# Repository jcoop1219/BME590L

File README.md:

# BME590L_Lightbulb - Design Skills Project (Variable Light Intensity)

See Final Working Video on [YouTube](https://youtu.be/NFrjT-VMIhY).

## Usage Guide
1. Turn on device using red I/O switch.
1. Push white button closest to I/O switch to cycle through light modes:
   + `Off`
   + `Brightest`
   + `Intermediate Brightness`
   + `Least Bright`
   + `Flashing @ 2 Hz`
1. Push and hold white button furthest from I/O switch to show the remaining voltage left in the battery on the adjacent LED:
   + `GREEN` = battery high (>8V)
   + `BLUE` = battery medium (7-8V)
   + `RED` = battery low (<7V)

## Battery Replacement
1. Spin flaps on bottom away from center of device.
1. Pull top of case off of bottom of case and disconnect toggle switch Molex connection from board.
1. Remove battery wire Molex connection from board.
1. Remove battery from battery slot.
1. Detach wired cap from battery.
1. Attach wired cap to new battery.
1. Add new battery to battery slot.
1. Re-attach battery wire Molex connection to board.
1. Reconnect toggle switch Molex connection to board.
1. Replace case top over case bottom (note: may need to use tweezers or small object to guide push buttons through case top).
1. Spin flaps on bottom towards center of device.

## Documentation
1. [Bill of Materials](https://github.com/jcoop1219/BME590L_Lightbulb/blob/master/Documentation/Bill%20of%20Materials.xlsx)
1. [Final Device Photos](https://github.com/jcoop1219/BME590L_Lightbulb/tree/master/Documentation/Final%20Device%20Photos)
1. [Testing Videos](https://github.com/jcoop1219/BME590L_Lightbulb/tree/master/Testing/Videos)

## Other Misc Notes:
+ Total weight = 9.9 oz
+ Current draw while on = 55 mA (lasts 7.2 hours on standard 9V battery)
+ Current draw while off = 0 mA (full off ensured by toggle I/O switch)

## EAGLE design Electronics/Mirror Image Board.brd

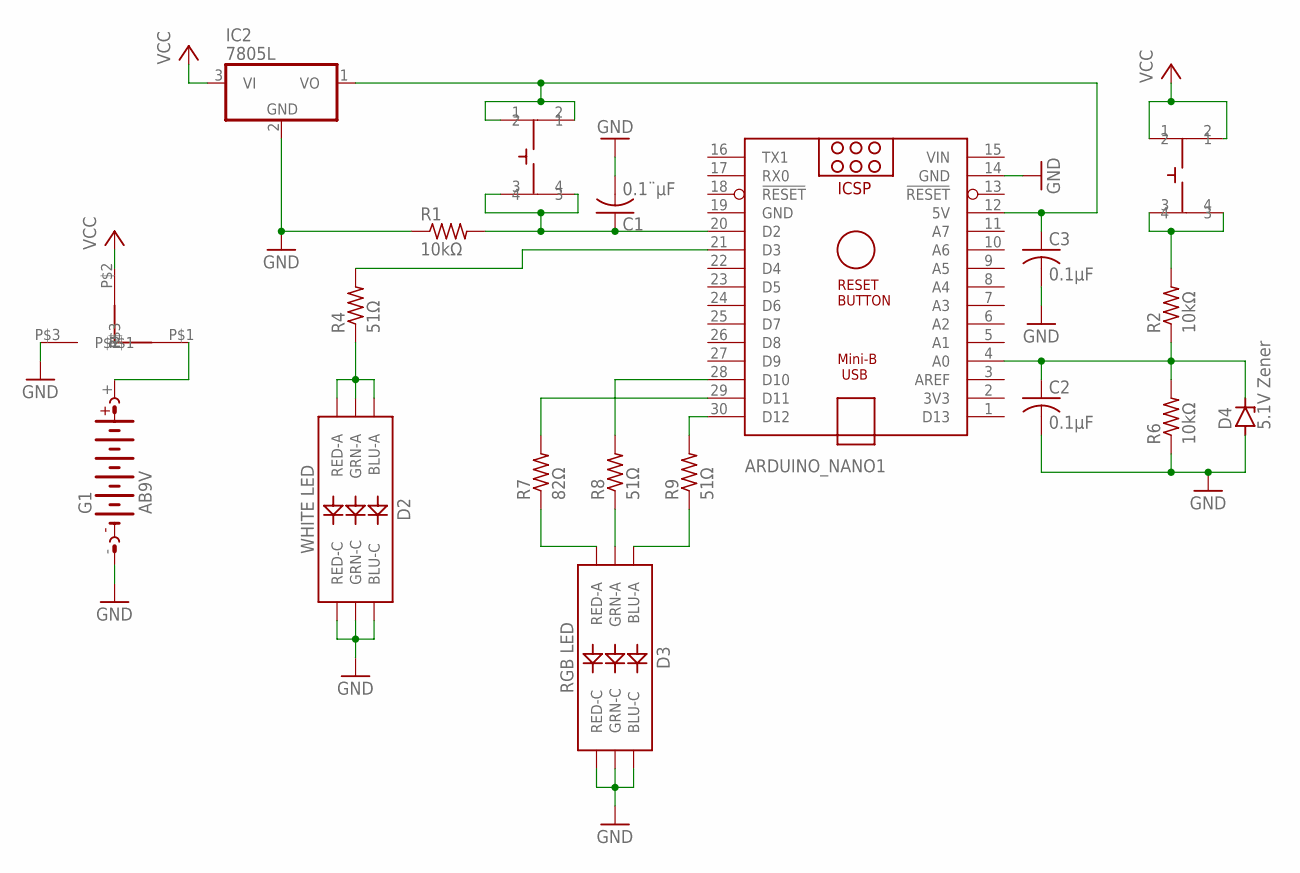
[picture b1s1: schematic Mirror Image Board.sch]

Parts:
ARDUINO_NANO1: ARDUINO_NANO
C1: 0.1¨µF; C0805
C2, C3: 0.1µF; C0805
D2: WHITE LED; LED-TRICOLOR-5050
D3: RGB LED; LED-TRICOLOR-5050
D4: 5.1V Zener; SOD64Z12
G1: AB9V
IC2: 7805L; TO92
R1, R2, R6: 10kΩ; R0805
R4, R8, R9: 51Ω; R0805
R7: 82Ω; R0805
U$1, U$2: SKRPABE010
U$3: DIPSWITCH

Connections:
GND: ARDUINO_NANO1.14 (GND), ARDUINO_NANO1.19 (GND), C1.2, C2.2, C3.2, D2.4 (BLU-C), D2.5 (RED-C), D2.6 (GRN-C), D3.4 (BLU-C), D3.5 (RED-C), D3.6 (GRN-C), D4.A, G1.-, IC2.2 (GND), R1.1, R6.1, U$3.P$3
unnamed: G1.+, U$3.P$1
unnamed: ARDUINO_NANO1.30 (D12), R9.2
unnamed: ARDUINO_NANO1.20 (D2), C1.1, R1.2, U$1.3, U$1.4
unnamed: ARDUINO_NANO1.12 (5V), C3.1, IC2.1 (VO), U$1.1, U$1.2
unnamed: ARDUINO_NANO1.4 (A0), C2.1, D4.C, R2.1, R6.2
unnamed: R2.2, U$2.3, U$2.4
unnamed: ARDUINO_NANO1.21 (D3), R4.2
unnamed: ARDUINO_NANO1.29 (D11), R7.2
unnamed: D3.2 (RED-A), R7.1
unnamed: D3.1 (GRN-A), R8.1
unnamed: D3.3 (BLU-A), R9.1
unnamed: ARDUINO_NANO1.28 (D10), R8.2
unnamed: D2.1 (GRN-A), D2.2 (RED-A), D2.3 (BLU-A), R4.1
VCC: IC2.3 (VI), U$2.1, U$2.2, U$3.P$2
VIN: ARDUINO_NANO1.15 (VIN)

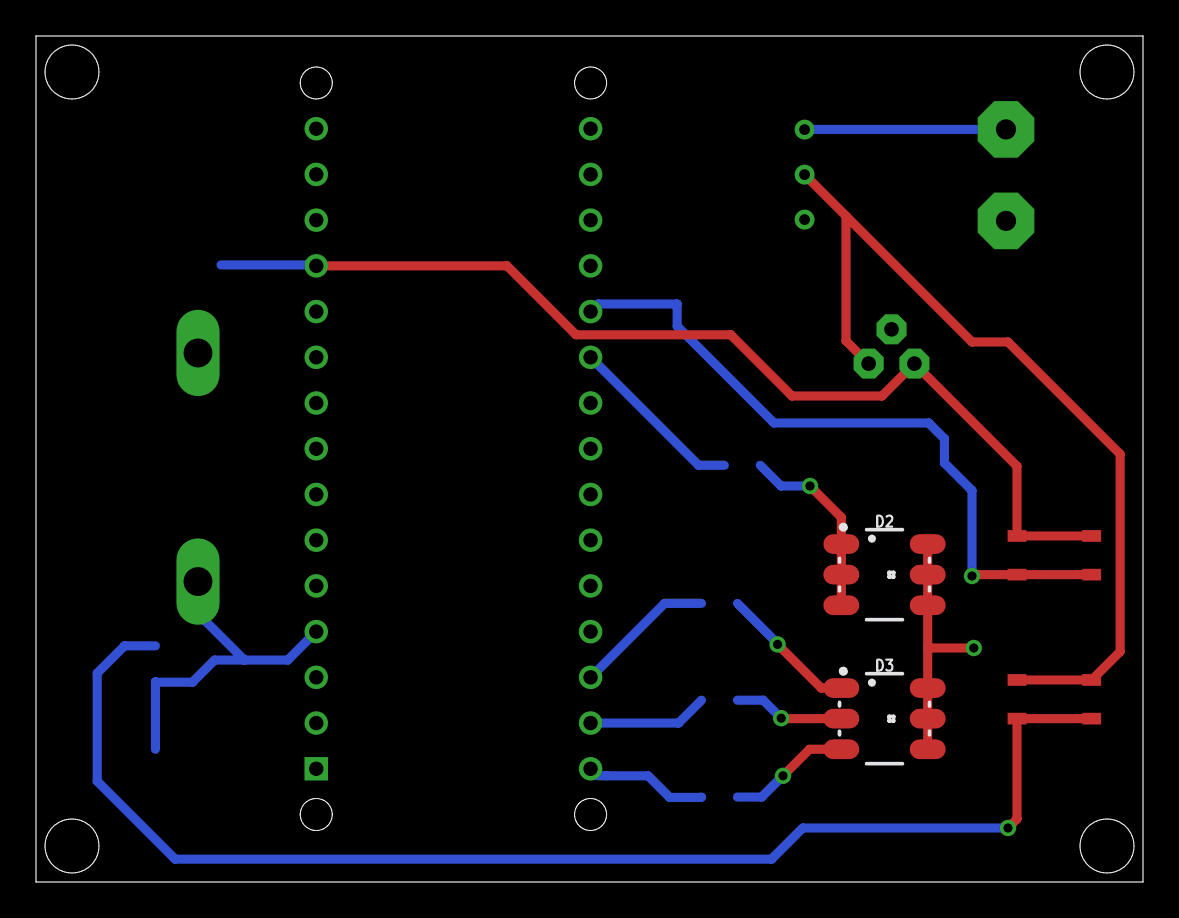
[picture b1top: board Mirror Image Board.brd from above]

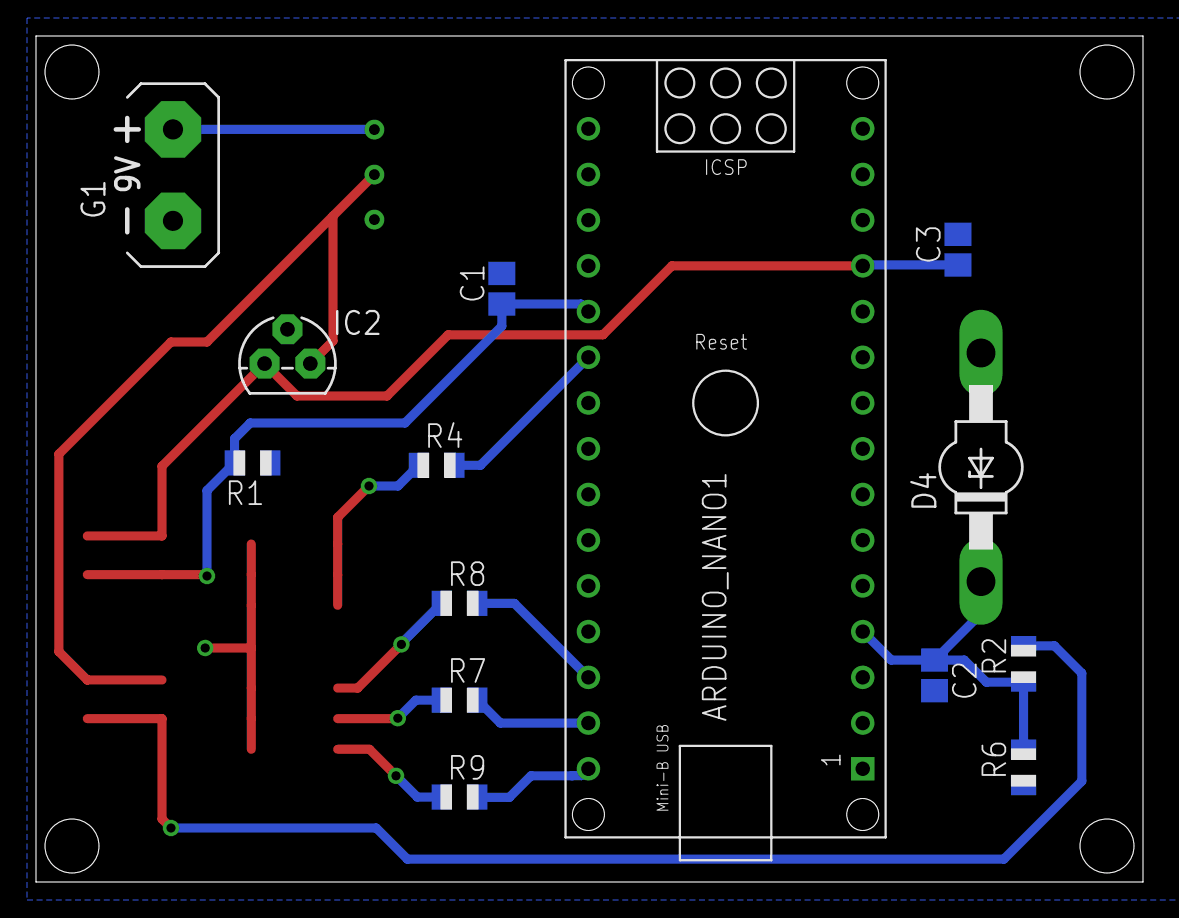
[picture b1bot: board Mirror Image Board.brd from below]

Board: 2 copper layers, 61.5 x 47.0 mm, 19 parts (15 on the bottom side), 15 nets.

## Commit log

2018-09-30 Creating directory structure
2018-10-02 uploading Functional Block Diagram and Physical Design
2018-11-01 Full circuit schematic and Arduino software flowchart
2018-11-08 Initial completion of EDA schematic, EDA circuit board, and Arduino code
2018-11-08 Actually committing Arduino script this time...
2018-11-08 Moving switches and LEDs to bottom side of board
2018-11-10 Adding some comments to code
2018-11-11 Updated board layout to put master switch on back and added connections for RGB LED
2018-11-12 Electronics parts datasheets
2018-11-13 Correcting pad placement and connections on PCB
2018-11-13 Finalizing Arduino script
2018-11-19 Moving small components further from MCU on board, tweaking ADC part of code for battery tester
2018-11-19 Updating board with custom-made footprints for push buttons
2018-11-19 correct spacing on pushbuttons
2018-11-19 adding light pipe spec sheet
2018-11-19 case mechanical drawings and 3D renderings
2018-11-19 removing pesky .DS_Store files
2018-11-27 Larger trace widths and new footprint for dip switch
2018-11-30 Correct trace widths this time (Matt Brown approved)
2018-12-03 Major updates to mechanical design based on etched PCB
2018-12-03 Integrated push button plunger and initial screw hole
2018-12-03 Added all screw holes
2018-12-03 updating a few resistor values for diodes to prevent draw of too much current from Arduino
2018-12-03 Changing resistor values and uploading mirror image of board
2018-12-04 Mechanical updates to incorporate new screw holes
2018-12-04 Adding testing data showing electronics working on PCB
2018-12-08 Fine tuning battery tester voltage thresholds
2018-12-08 Battery testing circuit video
2018-12-12 Mechanical redesign files
2018-12-12 Added mechanical flaps to hold box together
2018-12-12 Removing unused pieces of code
2018-12-12 Updating flashLED to blink without using a delay
2018-12-12 Adding comments to code and cleaning up code for readability
2018-12-13 Adding 9V battery spec sheet
2018-12-13 Adding pic showing circuit's current draw at full brightness
2018-12-13 Documentation updates and adding bill of materials
2018-12-13 Adding plunger track
2018-12-13 Using new type for lastFlashTime
2018-12-13 Adding video showing entire thing working in case
2018-12-13 Adding total weight pic
2018-12-14 Updated Bill of Materials
2018-12-14 Mechanical design folder re-org
2018-12-14 Testing data - photos and videos
2018-12-14 File reorganization
2018-12-14 File reorg
2018-12-14 Rename documentation folder

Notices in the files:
parts and their libraries:
SparkFun-LED: Licensing: Creative Commons ShareAlike 4.0 International - https://creativecommons.org/licenses/by-sa/4.0
